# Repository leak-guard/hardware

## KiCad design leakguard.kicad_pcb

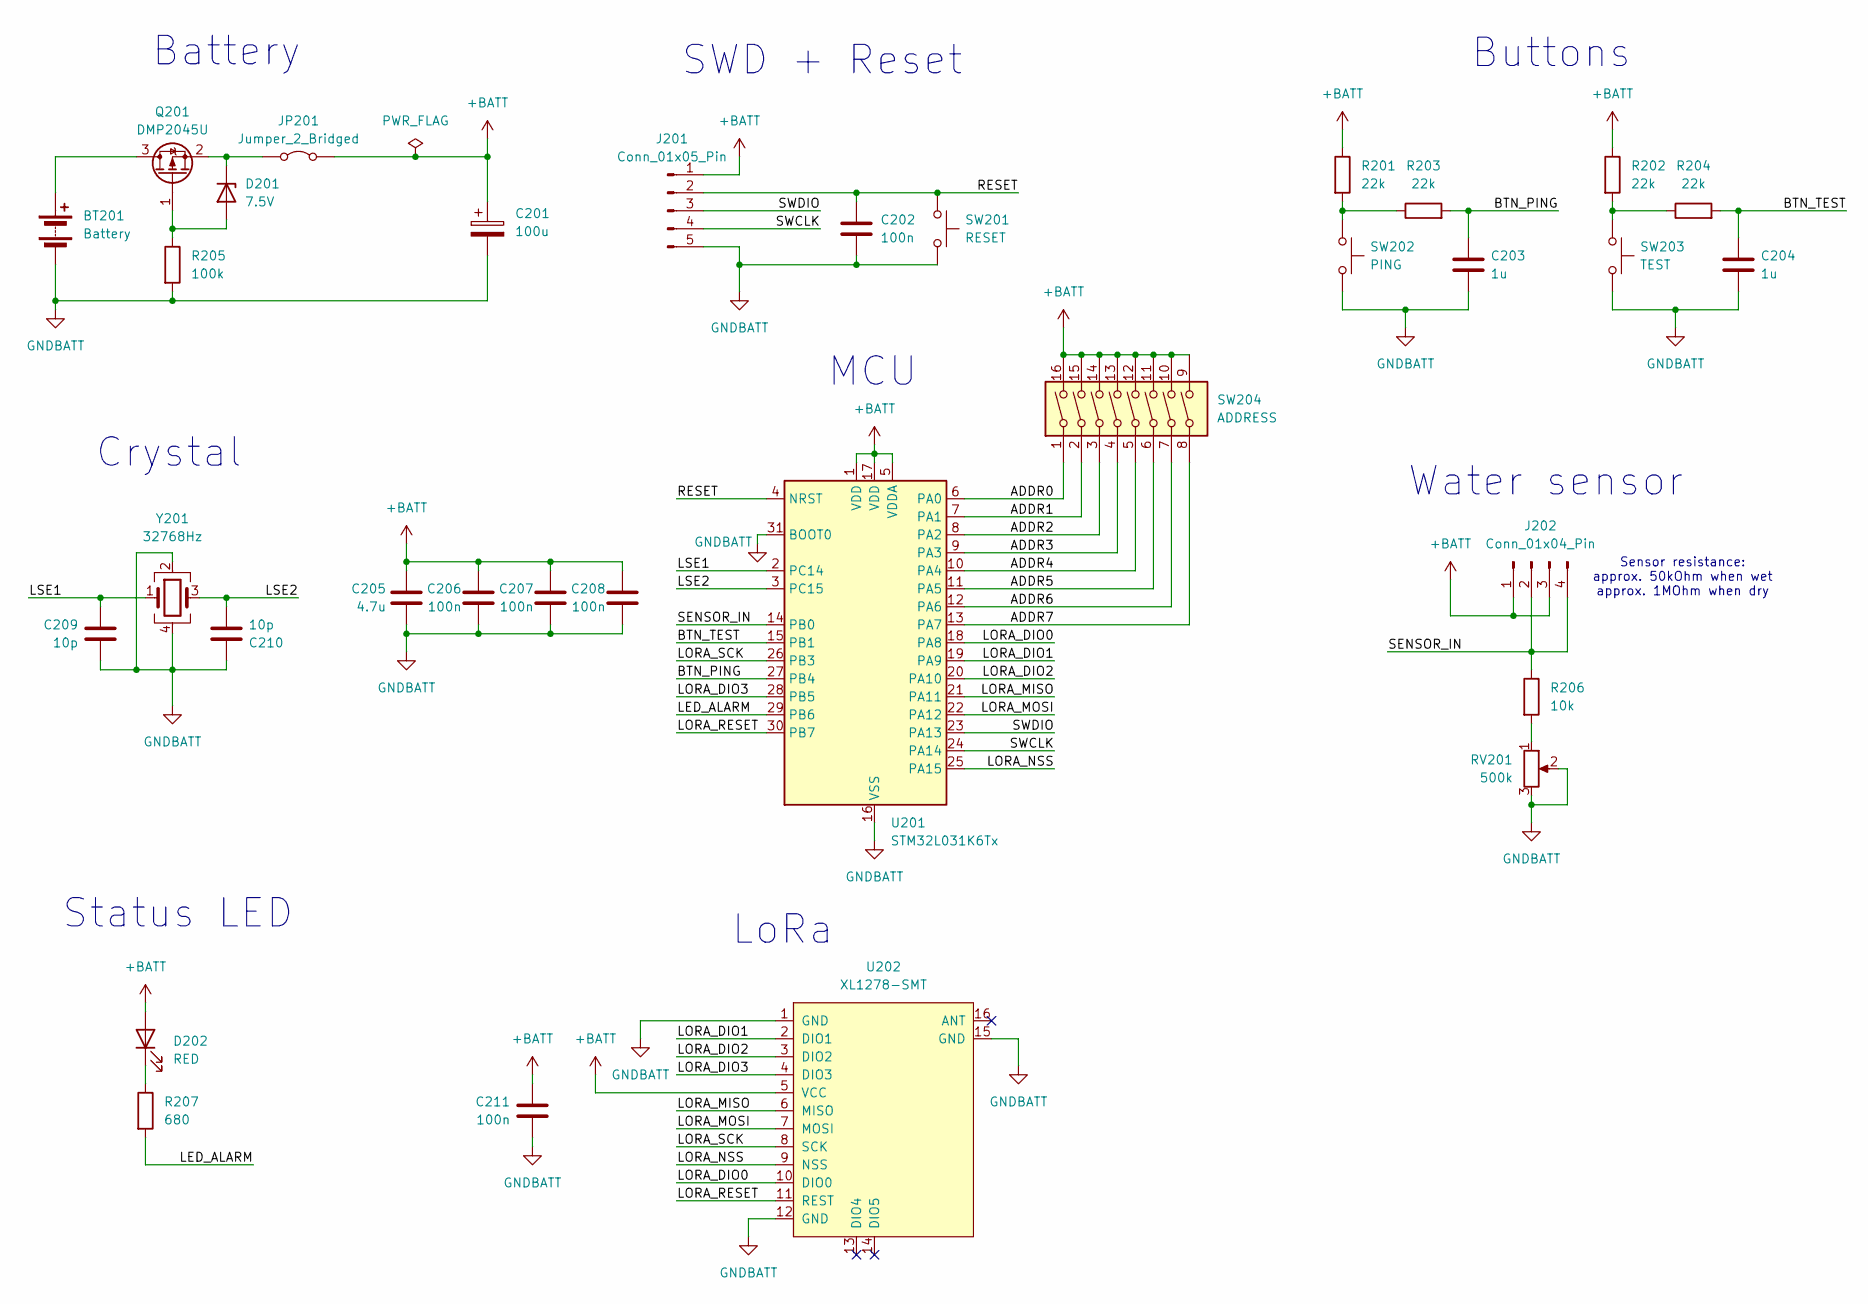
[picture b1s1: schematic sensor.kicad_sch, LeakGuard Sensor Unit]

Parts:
BT201: Battery; PinSocket_1x02_P2.54mm_Vertical
C201: 100u; CP_Radial_D5.0mm_P2.00mm
C202, C206, C207, C208, C211: 100n; C_0805_2012Metric_Pad1.18x1.45mm_HandSolder
C203, C204: 1u; C_0805_2012Metric_Pad1.18x1.45mm_HandSolder
C205: 4.7u; C_0805_2012Metric_Pad1.18x1.45mm_HandSolder
C209, C210: 10p; C_0805_2012Metric_Pad1.18x1.45mm_HandSolder
D201: 7.5V; D_SOD-523
D202: RED; LED_0805_2012Metric_Pad1.15x1.40mm_HandSolder
J201: Conn_01x05_Pin; PinHeader_1x05_P2.54mm_Vertical
J202: Conn_01x04_Pin; PinHeader_1x04_P2.54mm_Horizontal
JP201: Jumper_2_Bridged; PinHeader_1x02_P2.54mm_Horizontal
Q201: DMP2045U; SOT-23
R201, R202, R203, R204: 22k; R_0805_2012Metric_Pad1.20x1.40mm_HandSolder
R205: 100k; R_0805_2012Metric_Pad1.20x1.40mm_HandSolder
R206: 10k; R_0805_2012Metric_Pad1.20x1.40mm_HandSolder
R207: 680; R_0805_2012Metric_Pad1.20x1.40mm_HandSolder
RV201: 500k; Potentiometer_Piher_PT-6-V_Vertical
SW201: RESET; SW_Push_1P1T_NO_6x6mm_H9.5mm
SW202: PING; SW_Push_1P1T_NO_6x6mm_H9.5mm
SW203: TEST; SW_Push_1P1T_NO_6x6mm_H9.5mm
SW204: ADDRESS; SW_DIP_SPSTx08_Slide_9.78x22.5mm_W7.62mm_P2.54mm
U201: STM32L031K6Tx; LQFP-32_7x7mm_P0.8mm
U202: XL1278-SMT
Y201: 32768Hz; Oscillator_SMD_Abracon_ASDMB-4Pin_2.5x2.0mm

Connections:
+BATT: C201.1, C205.1, C206.1, C207.1, C208.1, C211.1, D202.2 (A), J201.1, J202.1, J202.3, JP201.2 (B), R201.1, R202.1, SW204.9, SW204.10, SW204.11, SW204.12, SW204.13, SW204.14, SW204.15, SW204.16, U201.1 (VDD), U201.5 (VDDA), U201.17 (VDD), U202.5 (VCC)
/Sensor unit/ADDR0: SW204.1, U201.6 (PA0)
/Sensor unit/ADDR1: SW204.2, U201.7 (PA1)
/Sensor unit/ADDR2: SW204.3, U201.8 (PA2)
/Sensor unit/ADDR3: SW204.4, U201.9 (PA3)
/Sensor unit/ADDR4: SW204.5, U201.10 (PA4)
/Sensor unit/ADDR5: SW204.6, U201.11 (PA5)
/Sensor unit/ADDR6: SW204.7, U201.12 (PA6)
/Sensor unit/ADDR7: SW204.8, U201.13 (PA7)
/Sensor unit/BTN_PING: C203.1, R203.2, U201.27 (PB4)
/Sensor unit/BTN_TEST: C204.1, R204.2, U201.15 (PB1)
/Sensor unit/LED_ALARM: R207.2, U201.29 (PB6)
/Sensor unit/LORA_DIO0: U201.18 (PA8), U202.10 (DIO0)
/Sensor unit/LORA_DIO1: U201.19 (PA9), U202.2 (DIO1)
/Sensor unit/LORA_DIO2: U201.20 (PA10), U202.3 (DIO2)
/Sensor unit/LORA_DIO3: U201.28 (PB5), U202.4 (DIO3)
/Sensor unit/LORA_MISO: U201.21 (PA11), U202.6 (MISO)
/Sensor unit/LORA_MOSI: U201.22 (PA12), U202.7 (MOSI)
/Sensor unit/LORA_NSS: U201.25 (PA15), U202.9 (NSS)
/Sensor unit/LORA_RESET: U201.30 (PB7), U202.11 (REST)
/Sensor unit/LORA_SCK: U201.26 (PB3), U202.8 (SCK)
/Sensor unit/LSE1: C209.1, U201.2 (PC14), Y201.1
/Sensor unit/LSE2: C210.2, U201.3 (PC15), Y201.3
/Sensor unit/RESET: C202.1, J201.2, SW201.1, U201.4 (NRST)
/Sensor unit/SENSOR_IN: J202.2, J202.4, R206.1, U201.14 (PB0)
/Sensor unit/SWCLK: J201.4, U201.24 (PA14)
/Sensor unit/SWDIO: J201.3, U201.23 (PA13)
GNDBATT: BT201.2 (-), C201.2, C202.2, C203.2, C204.2, C205.2, C206.2, C207.2, C208.2, C209.2, C210.1, C211.2, J201.5, R205.2, RV201.2, RV201.3, SW201.2, SW202.2, SW203.2, U201.16 (VSS), U201.31 (BOOT0), U201.32 (VSS), U202.1 (GND), U202.12 (GND), U202.15 (GND), Y201.2, Y201.4
unnamed: BT201.1 (+), Q201.3 (D)
unnamed: D201.2 (A), Q201.1 (G), R205.1
unnamed: D201.1 (K), JP201.1 (A), Q201.2 (S)
unnamed: D202.1 (K), R207.1
unnamed: R201.2, R203.1, SW202.1
unnamed: R202.2, R204.1, SW203.1
unnamed: R206.2, RV201.1

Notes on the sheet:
Battery
Water sensor
Buttons
Sensor resistance: approx. 50kOhm when wet approx. 1MOhm when dry
Status LED
SWD + Reset
LoRa
MCU
Crystal

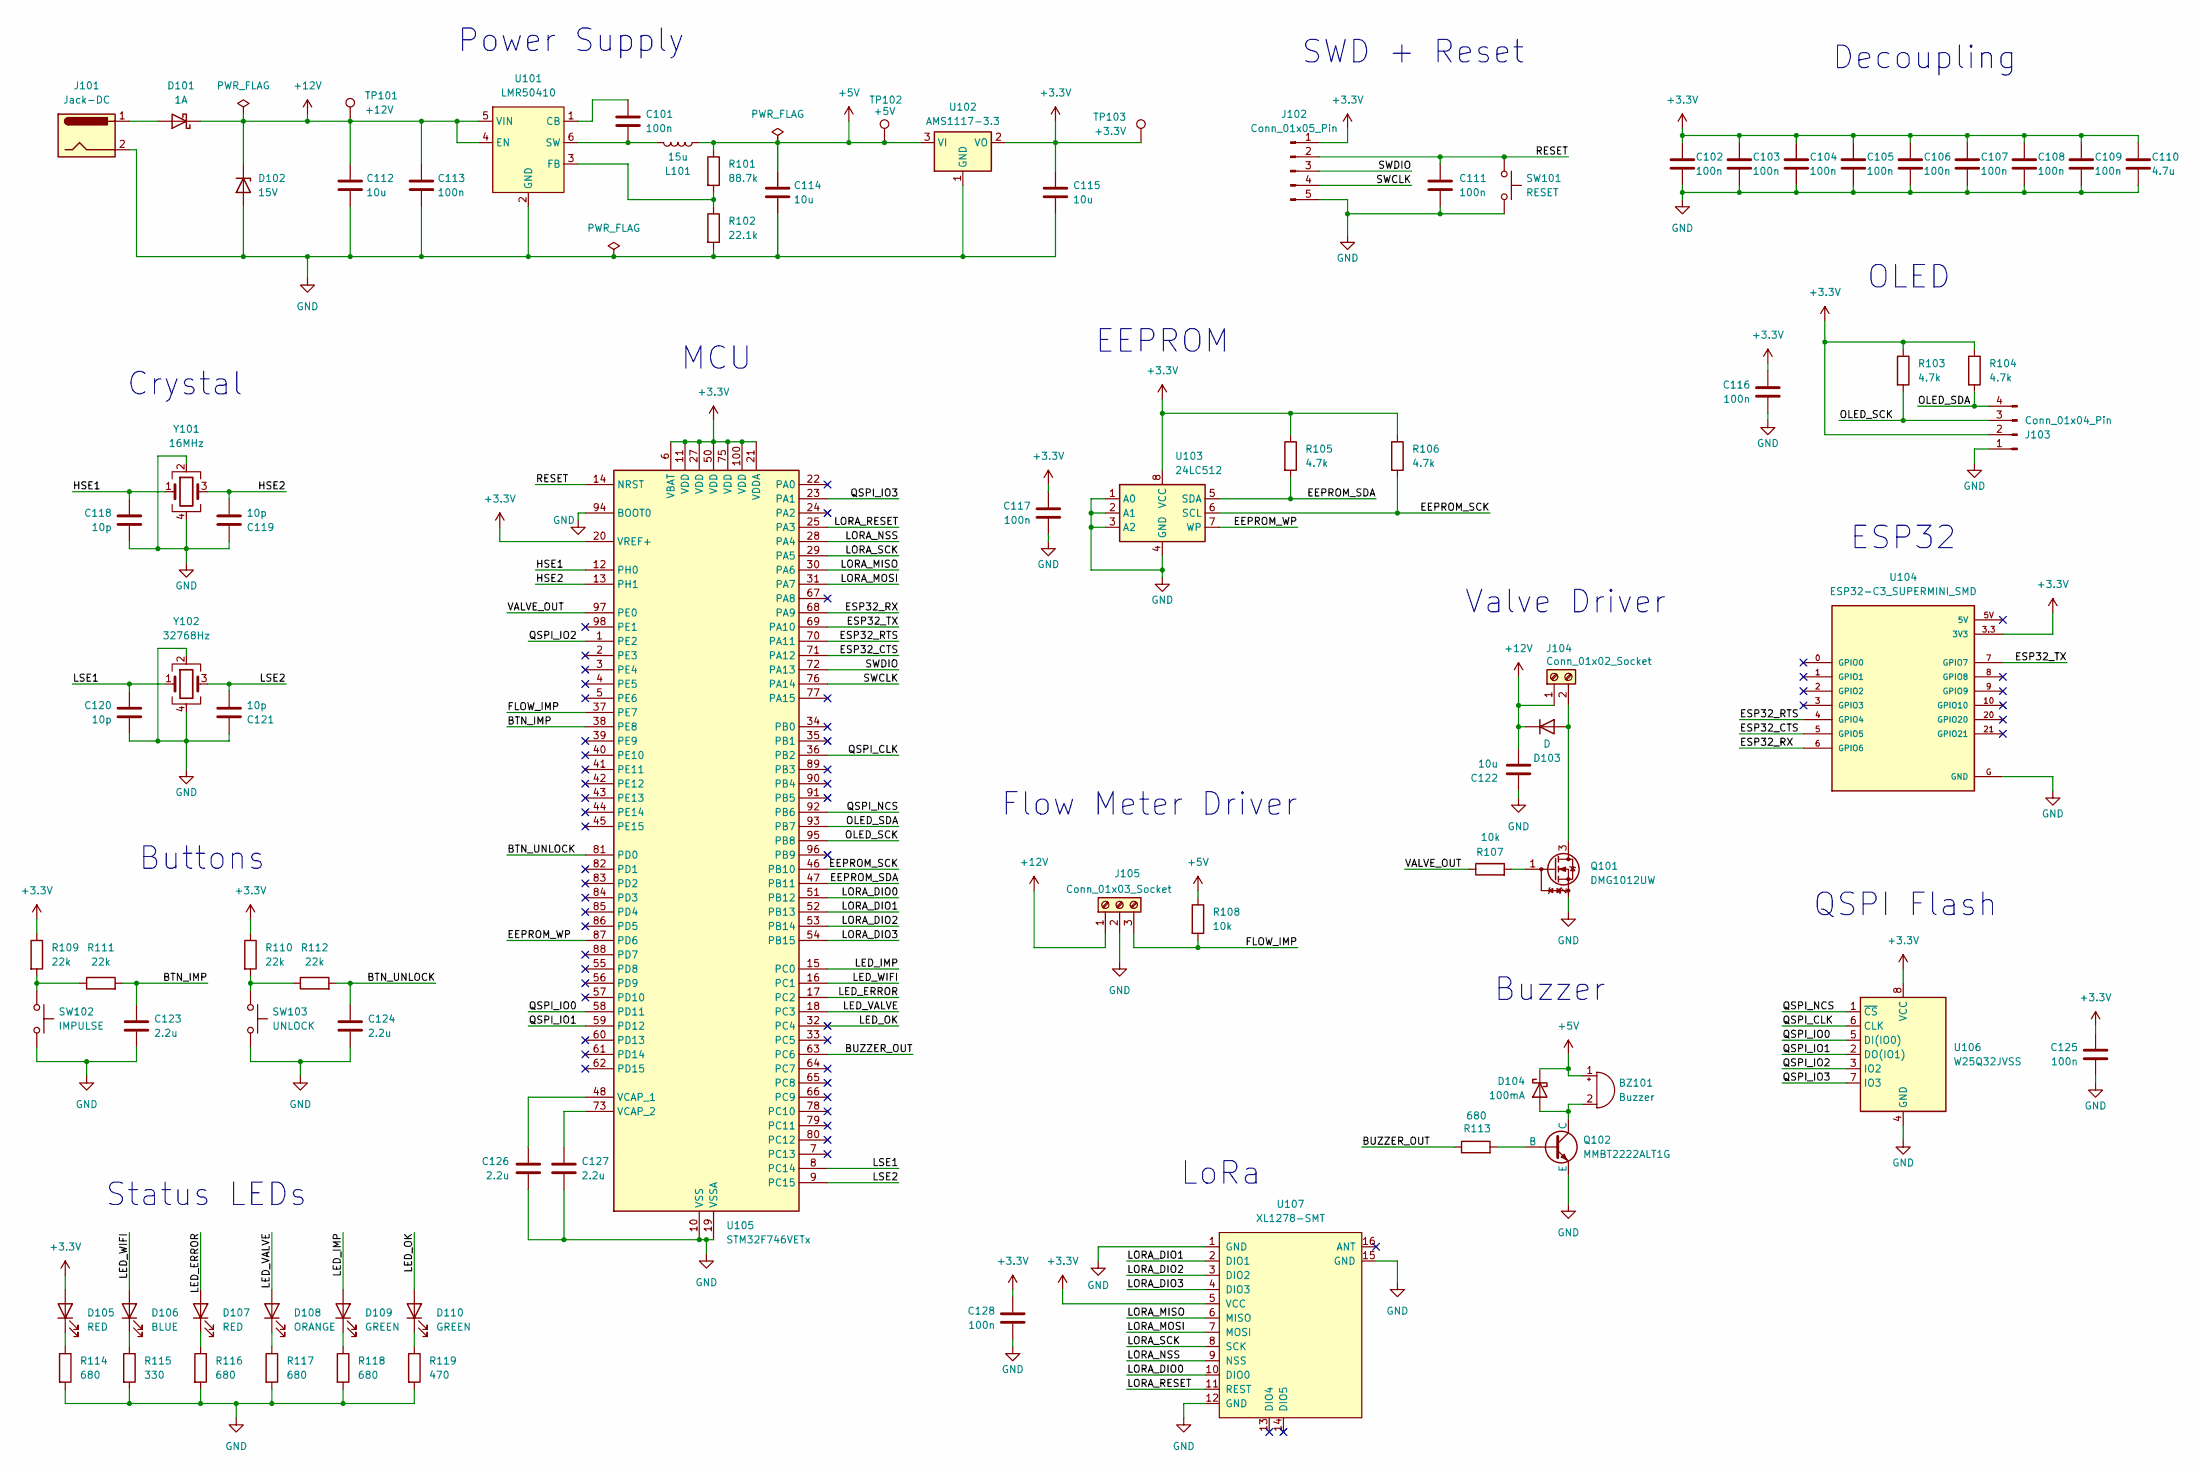
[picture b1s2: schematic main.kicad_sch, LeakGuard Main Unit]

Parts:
BZ101: Buzzer; Buzzer_TDK_PS1240P02BT_D12.2mm_H6.5mm
C101, C102, C103, C104, C105, C106, C107, C108, C109, C111, C113, C116, C117, C125, C128: 100n; C_0805_2012Metric_Pad1.18x1.45mm_HandSolder
C110: 4.7u; C_0805_2012Metric_Pad1.18x1.45mm_HandSolder
C112, C114, C115, C122: 10u; C_0805_2012Metric_Pad1.18x1.45mm_HandSolder
C118, C119, C120, C121: 10p; C_0805_2012Metric_Pad1.18x1.45mm_HandSolder
C123, C124, C126, C127: 2.2u; C_0805_2012Metric_Pad1.18x1.45mm_HandSolder
D101: 1A; D_SOD-123
D102: 15V; D_PowerDI-123
D103: D; D_SOD-123
D104: 100mA; D_SOD-123
D105, D107: RED; LED_D3.0mm
D106: BLUE; LED_D3.0mm
D108: ORANGE; LED_D3.0mm
D109: GREEN; LED_0805_2012Metric_Pad1.15x1.40mm_HandSolder
D110: GREEN; LED_D3.0mm
J101: Jack-DC; BarrelJack_CUI_PJ-036AH-SMT_Horizontal
J102: Conn_01x05_Pin; PinHeader_1x05_P2.54mm_Vertical
J103: Conn_01x04_Pin; PinHeader_1x04_P2.54mm_Vertical
J104: Conn_01x02_Socket; TerminalBlock_4Ucon_1x02_P3.50mm_Horizontal
J105: Conn_01x03_Socket; TerminalBlock_4Ucon_1x03_P3.50mm_Horizontal
L101: 15u; L_Vishay_IHLP-1616
Q101: DMG1012UW; SOT-323_SC-70
Q102: MMBT2222ALT1G; SOT-23-3
R101: 88.7k; R_0805_2012Metric_Pad1.20x1.40mm_HandSolder
R102: 22.1k; R_0805_2012Metric_Pad1.20x1.40mm_HandSolder
R103, R104, R105, R106: 4.7k; R_0805_2012Metric_Pad1.20x1.40mm_HandSolder
R107, R108: 10k; R_0805_2012Metric_Pad1.20x1.40mm_HandSolder
R109, R110, R111, R112: 22k; R_0805_2012Metric_Pad1.20x1.40mm_HandSolder
R113, R114, R116, R117, R118: 680; R_0805_2012Metric_Pad1.20x1.40mm_HandSolder
R115: 330; R_0805_2012Metric_Pad1.20x1.40mm_HandSolder
R119: 470; R_0805_2012Metric_Pad1.20x1.40mm_HandSolder
SW101: RESET; SW_Push_1P1T_NO_6x6mm_H9.5mm
SW102: IMPULSE; SW_Push_1P1T_NO_6x6mm_H9.5mm
SW103: UNLOCK; SW_Push_1P1T_NO_6x6mm_H9.5mm
TP101: +12V; TestPoint_Pad_D1.5mm
TP102: +5V; TestPoint_Pad_D1.5mm
TP103: +3.3V; TestPoint_Pad_D1.5mm
U101: LMR50410; SOT-23-6_Handsoldering
U102: AMS1117-3.3; SOT-223-3_TabPin2
U103: 24LC512; SOIC-8_3.9x4.9mm_P1.27mm
U104: ESP32-C3_SUPERMINI_SMD; MODULE_ESP32-C3_SUPERMINI
U105: STM32F746VETx; LQFP-100_14x14mm_P0.5mm
U106: W25Q32JVSS; SOIC-8_5.23x5.23mm_P1.27mm
U107: XL1278-SMT
Y101: 16MHz; Oscillator_SMD_Abracon_ASDMB-4Pin_2.5x2.0mm
Y102: 32768Hz; Oscillator_SMD_Abracon_ASDMB-4Pin_2.5x2.0mm

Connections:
+3.3V: C102.1, C103.1, C104.1, C105.1, C106.1, C107.1, C108.1, C109.1, C110.1, C115.1, C116.1, C117.1, C125.1, C128.1, D105.2 (A), J102.1, J103.2, R103.1, R104.1, R105.1, R106.1, R109.1, R110.1, TP103.1, U102.2 (VO), U103.8 (VCC), U104.3.3 (3V3), U105.6 (VBAT), U105.11 (VDD), U105.20 (VREF+), U105.21 (VDDA), U105.27 (VDD), U105.50 (VDD), U105.75 (VDD), U105.100 (VDD), U106.8 (VCC), U107.5 (VCC)
+5V: BZ101.1 (+), C114.1, D104.1 (K), L101.2, R101.1, R108.1, TP102.1, U102.3 (VI)
+12V: C112.1, C113.1, C122.2, D101.1 (K), D102.1 (K), D103.1 (K), J104.1, J105.1, TP101.1, U101.4 (EN), U101.5 (VIN)
/Main unit/BTN_IMP: C123.1, R111.2, U105.38 (PE8)
/Main unit/BTN_UNLOCK: C124.1, R112.2, U105.81 (PD0)
/Main unit/BUZZER_OUT: R113.1, U105.63 (PC6)
/Main unit/EEPROM_SCK: R106.2, U103.6 (SCL), U105.46 (PB10)
/Main unit/EEPROM_SDA: R105.2, U103.5 (SDA), U105.47 (PB11)
/Main unit/EEPROM_WP: U103.7 (WP), U105.87 (PD6)
/Main unit/ESP32_CTS: U104.5 (GPIO5), U105.71 (PA12)
/Main unit/ESP32_RTS: U104.4 (GPIO4), U105.70 (PA11)
/Main unit/ESP32_RX: U104.6 (GPIO6), U105.68 (PA9)
/Main unit/ESP32_TX: U104.7 (GPIO7), U105.69 (PA10)
/Main unit/FLOW_IMP: J105.3, R108.2, U105.37 (PE7)
/Main unit/HSE1: C118.1, U105.12 (PH0), Y101.1
/Main unit/HSE2: C119.2, U105.13 (PH1), Y101.3
/Main unit/LED_ERROR: D107.2 (A), U105.17 (PC2)
/Main unit/LED_IMP: D109.2 (A), U105.15 (PC0)
/Main unit/LED_OK: D110.2 (A), U105.32 (PC4)
/Main unit/LED_VALVE: D108.2 (A), U105.18 (PC3)
/Main unit/LED_WIFI: D106.2 (A), U105.16 (PC1)
/Main unit/LORA_DIO0: U105.51 (PB12), U107.10 (DIO0)
/Main unit/LORA_DIO1: U105.52 (PB13), U107.2 (DIO1)
/Main unit/LORA_DIO2: U105.53 (PB14), U107.3 (DIO2)
/Main unit/LORA_DIO3: U105.54 (PB15), U107.4 (DIO3)
/Main unit/LORA_MISO: U105.30 (PA6), U107.6 (MISO)
/Main unit/LORA_MOSI: U105.31 (PA7), U107.7 (MOSI)
/Main unit/LORA_NSS: U105.28 (PA4), U107.9 (NSS)
/Main unit/LORA_RESET: U105.25 (PA3), U107.11 (REST)
/Main unit/LORA_SCK: U105.29 (PA5), U107.8 (SCK)
/Main unit/LSE1: C120.1, U105.8 (PC14), Y102.1
/Main unit/LSE2: C121.2, U105.9 (PC15), Y102.3
/Main unit/OLED_SCK: J103.3, R103.2, U105.95 (PB8)
/Main unit/OLED_SDA: J103.4, R104.2, U105.93 (PB7)
/Main unit/QSPI_CLK: U105.36 (PB2), U106.6 (CLK)
/Main unit/QSPI_IO0: U105.58 (PD11), U106.5 (DI(IO0))
/Main unit/QSPI_IO1: U105.59 (PD12), U106.2 (DO(IO1))
/Main unit/QSPI_IO2: U105.1 (PE2), U106.3 (IO2)
/Main unit/QSPI_IO3: U105.23 (PA1), U106.7 (IO3)
/Main unit/QSPI_NCS: U105.92 (PB6), U106.1 (~CS)
/Main unit/RESET: C111.1, J102.2, SW101.1, U105.14 (NRST)
/Main unit/SWCLK: J102.4, U105.76 (PA14)
/Main unit/SWDIO: J102.3, U105.72 (PA13)
/Main unit/VALVE_OUT: R107.1, U105.97 (PE0)
GND: C102.2, C103.2, C104.2, C105.2, C106.2, C107.2, C108.2, C109.2, C110.2, C111.2, C112.2, C113.2, C114.2, C115.2, C116.2, C117.2, C118.2, C119.1, C120.2, C121.1, C122.1, C123.2, C124.2, C125.2, C126.2, C127.2, C128.2, D102.2 (A), J101.2, J102.5, J103.1, J105.2, Q101.2 (S), Q102.3 (E), R102.2, R114.2, R115.2, R116.2, R117.2, R118.2, R119.2, SW101.2, SW102.2, SW103.2, U101.2 (GND), U102.1 (GND), U103.1 (A0), U103.2 (A1), U103.3 (A2), U103.4 (GND), U104.G (GND), U105.10 (VSS), U105.19 (VSSA), U105.26 (VSS), U105.49 (VSS), U105.74 (VSS), U105.94 (BOOT0), U105.99 (VSS), U106.4 (GND), U107.1 (GND), U107.12 (GND), U107.15 (GND), Y101.2, Y101.4, Y102.2, Y102.4
unnamed: BZ101.2 (-), D104.2 (A), Q102.1 (C)
unnamed: D101.2 (A), J101.1
unnamed: D103.2 (A), J104.2, Q101.3 (D)
unnamed: D105.1 (K), R114.1
unnamed: D106.1 (K), R115.1
unnamed: D107.1 (K), R116.1
unnamed: D108.1 (K), R117.1
unnamed: D109.1 (K), R118.1
unnamed: D110.1 (K), R119.1
unnamed: Q101.1 (G), R107.2
unnamed: Q102.2 (B), R113.2
unnamed: R109.2, R111.1, SW102.1
unnamed: R110.2, R112.1, SW103.1
unnamed: C101.1, U101.1 (CB)
unnamed: R101.2, R102.1, U101.3 (FB)
unnamed: C101.2, L101.1, U101.6 (SW)
unnamed: C126.1, U105.48 (VCAP_1)
unnamed: C127.1, U105.73 (VCAP_2)

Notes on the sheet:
Flow Meter Driver
QSPI Flash
SWD + Reset
Valve Driver
Buttons
Power Supply
Decoupling
LoRa
EEPROM
MCU
Buzzer
ESP32
Crystal
Status LEDs
OLED

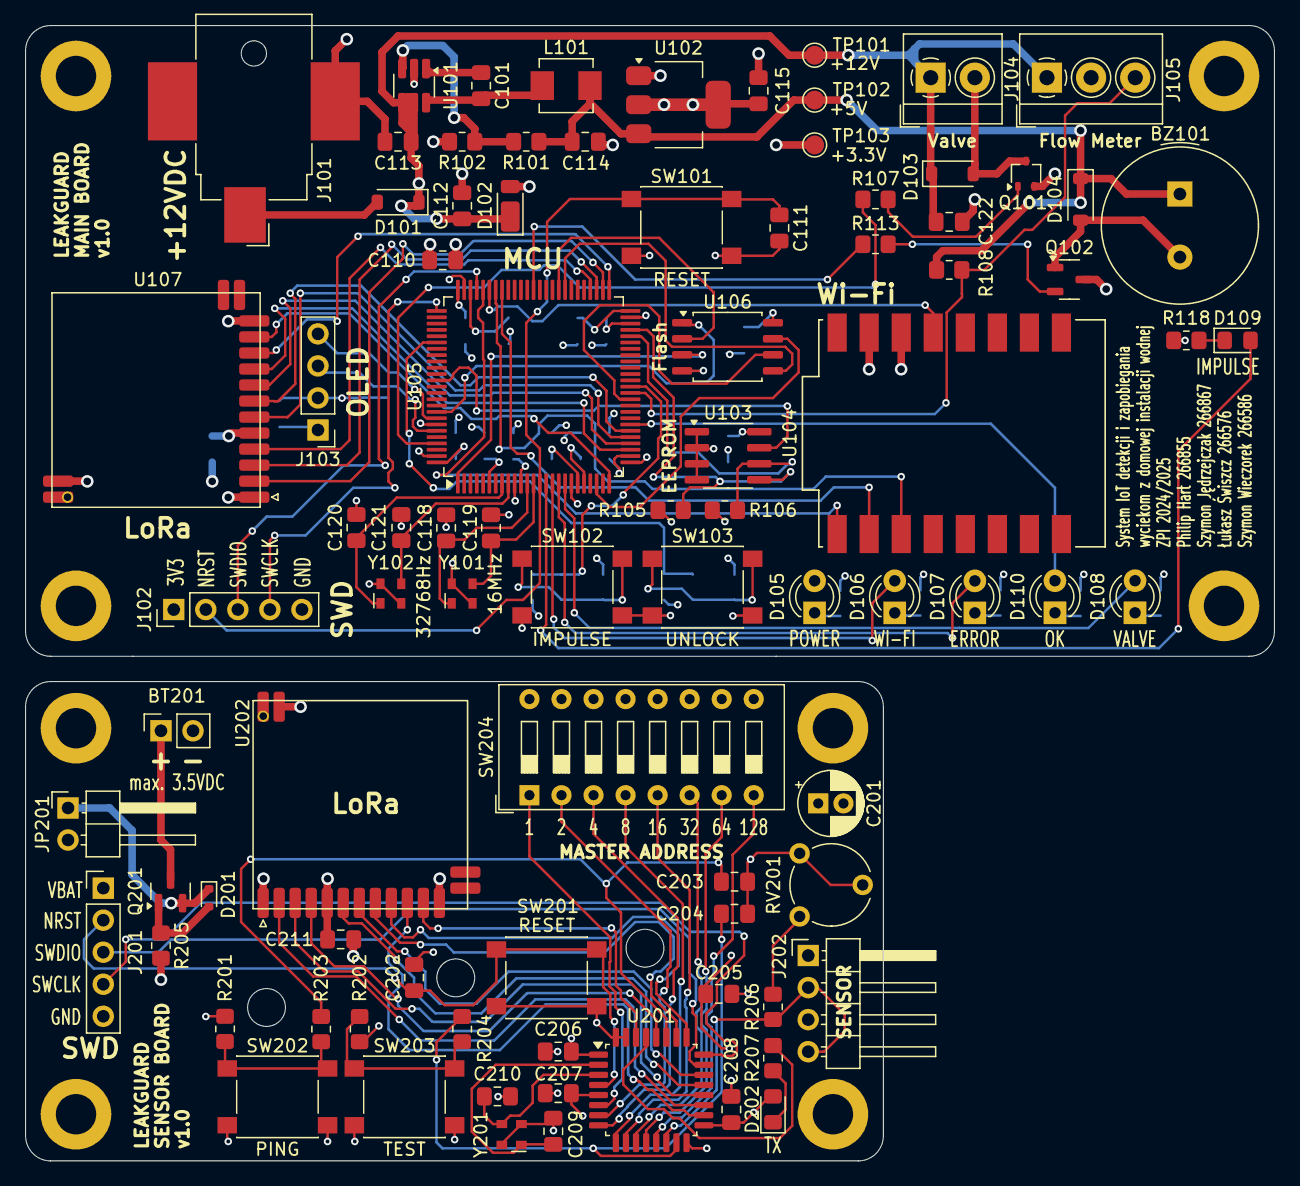
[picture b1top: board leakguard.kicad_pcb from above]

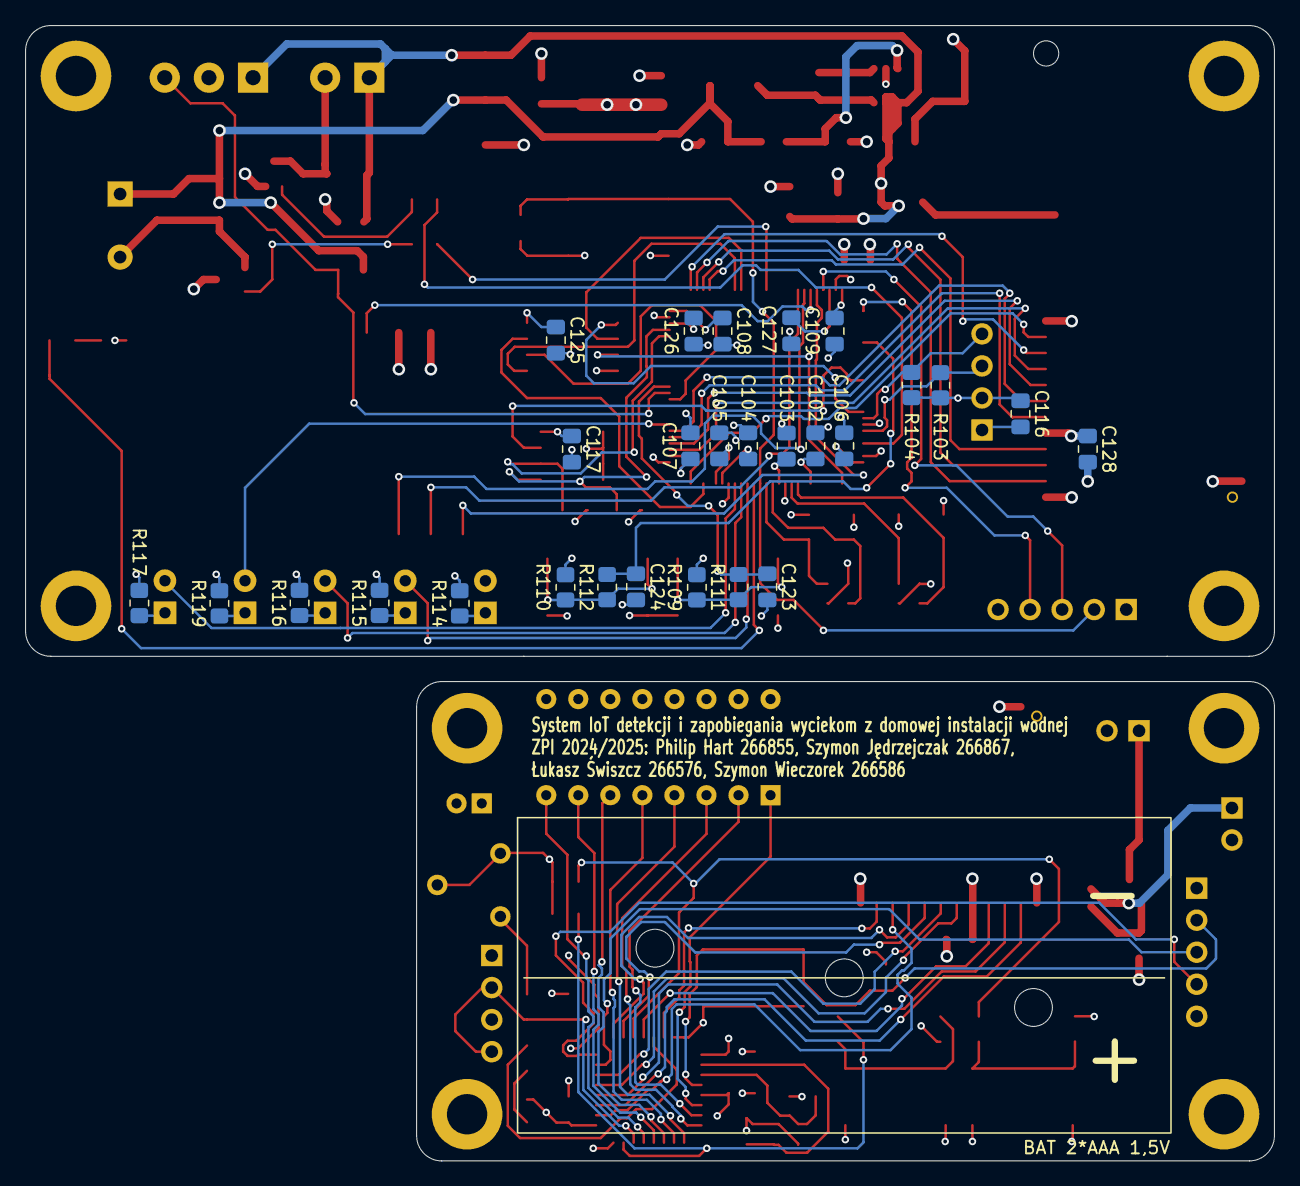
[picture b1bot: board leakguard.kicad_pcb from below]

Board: 4 copper layers, 99.0 x 90.0 mm, 115 parts (28 on the bottom side), 98 nets.

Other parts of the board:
BAT 2*AAA 1,5V: BatteryHolder

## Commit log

2024-10-13 Upload first version of the HW project
2024-10-15 Final version sent to production
